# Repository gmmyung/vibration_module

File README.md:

# OFBGlove: Open-Finger-Braille Glove 시스템

시청각장애인을 위한 실시간 양방향 독립 소통 지원 웨어러블 촉각 시스템

## 개요

**OFBGlove**는 시청각장애인(Deafblind)을 위한 혁신적인 소통 보조 시스템입니다. 음성과 환경 소리를 실시간 6점 점자 패턴으로 변환하여 촉각 피드백을 제공하며, 양방향 통신을 통해 독립적인 의사소통을 가능하게 합니다.

### 핵심 개념

시청각장애인들은 손가락 점자(finger-braille)와 같은 촉각 소통 방법을 사용하지만, 이는 훈련된 통역자와의 직접적인 신체 접촉이 필요합니다.
또한 기존 단말기 등은 일상생활, 돌아다니면서 사용하기에 손이 묶이는 등 동시에 사용할 수 없다는 큰 제약을 갖고 있습니다.

OFBGlove는 이러한 한계를 극복하기 위해:

- **손가락 끝이 노출된 반장갑 형태의 디자인**: 일상적인 촉각 활동을 방해하지 않으며 상시 사용 가능
- **실시간 감각 대체**: 음성 → 촉각 변환 (<300ms 지연)
- **양방향 통신**: 점자 입력 → 음성 출력 지원
- **독립적 사용**: 전문 통역인 없이도 실시간 독립 사용 가능

---

## 시스템 아키텍처

```
┌──────────────────────────────────────────────────────────────┐
│                    OFBGlove 시스템                            │
├──────────────────────────────────────────────────────────────┤
│                                                              │
│  음성/환경 소리 입력                                           │
│        ↓                                                     │
│  Sensory Substitution Module (Android App)                   │
│        ├─ STT (Speech-to-Text)                               │
│        ├─ TTB (Text-to-Braille)                              │
│        ├─ 환경 소리 감지                                      │
│        └─ BTT/TTS (Braille-to-Text/Speech)                   │
│        ↓                                                     │
│  통신 계층 (BLE/WiFi)                                         │
│        ├─ BLE: 2-byte 바이너리 프로토콜                        │
│        └─ WiFi: WebSocket 실시간 통신                         │
│        ↓                                                     │
│  Wearable Haptic Module                                      │
│        ├─ ESP32 기반 점자 장갑 (6개 진동 모터, 입력 장치)       │
│        └─ 웹 비주얼라이저 (시연/교육용)                        │
│                                                              │
└──────────────────────────────────────────────────────────────┘
```

---

## 프로젝트 구조

### 1. `application/` - Android 애플리케이션

**Sensory Substitution Module의 핵심 구현체**

#### 주요 기능
- **음성 인식 (STT)**: 실시간 음성을 텍스트로 변환
- **점자 변환 (TTB/BTT)**: liblouis-java 기반 양방향 변환
  - 6점 점자 시스템 지원
  - 다국어 점자 테이블
  - 실시간 변환 (<10ms)
- **음성 합성 (TTS)**: 변환된 텍스트를 음성으로 변환
- **통신 프로토콜**:
  - **BLE GATT**: 최적화된 2-byte 바이너리 프로토콜
  - **WiFi Socket**: JSON 기반 확장 프로토콜
- **점자 입력**: 6-dot 인터랙티브 그리드
- **UI/UX**: Jetpack Compose + Material Design 3

#### 기술 스택
```yaml
플랫폼: Android 11+ (API 30+)
언어: Kotlin 2.0.21
UI: Jetpack Compose + Material Design 3
아키텍처: MVVM + StateFlow + Coroutines
점자 변환: liblouis-java 5.1.0
통신: BLE GATT, WiFi Socket, WebSocket
```

#### 빠른 시작
```bash
cd application
# Android Studio에서 프로젝트 열기
# Gradle 동기화 후 빌드
# Android 기기에 설치
```

#### 권한 요구사항
- `RECORD_AUDIO`: 음성 인식
- `BLUETOOTH_CONNECT`, `BLUETOOTH_SCAN`: BLE 통신
- `INTERNET`, `ACCESS_NETWORK_STATE`: WiFi 통신
- `VIBRATE`: 햅틱 피드백

---

### 2. `web_visualizer/` - 웹 비주얼라이저

**장갑 없이도 시스템을 시연하고 체험할 수 있는 웹 인터페이스**

#### 주요 특징
- **교육/시연 목적**: 물리적 장갑 없이도 완전한 데모 가능
- **실시간 점자, 장갑 시각화**: 장갑 이미지 위에 6개 점 표시
- **양방향 통신**: 입력과 출력 인터페이스
- **WebSocket, BLE 통신**: 실시간 점자 패턴 송수신
- **레이아웃 제어**: 사용자 정의 가능한 인터페이스
- **반응형 디자인**: 모바일/태블릿/데스크톱 최적화

#### 기술 스택
```yaml
프레임워크: React 18 + TypeScript
통신: WebSocket (ws://localhost:8000)
스타일링: CSS3 + Responsive Design
빌드 도구: Create React App
```

#### 개발 서버 실행
```bash
# 웹 비주얼라이저 실행
cd web_visualizer
npm install
npm start
```

#### 프로젝트 구조
```
web_visualizer/
├── src/
│   ├── components/
│   │   ├── BrailleDot.tsx          # 개별 점자 점
│   │   ├── BrailleGrid.tsx         # 6-dot 그리드
│   │   ├── BrailleCell.tsx         # 점자 셀 (2×3)
│   │   ├── ConnectionStatus.tsx    # 연결 상태
│   │   └── OFBGloveVisualizer.tsx  # 메인 컴포넌트
│   ├── services/
│   │   ├── WebSocketService.ts     # WebSocket 관리
│   │   └── BrailleProtocol.ts      # 프로토콜 처리
│   └── types/
│       ├── braille.ts              # 점자 타입
│       └── layout.ts               # 레이아웃 타입
└── public/
    └── OFBGlove_image.png          # 장갑 이미지
```

---

### 3. `wearable/` - ESP32 장갑 제어

**Wearable Haptic Module의 하드웨어 구현체**

#### 주요 컴포넌트
- **ESP32 MCU**: 양방향 통신 및 모터 제어
- **BLE Server**: Android 앱과의 실시간 통신
- **WiFi Client**: 웹 비주얼라이저 연동
- **진동 모터**: 6개 점자 점 표현
- **버튼 센서**: 사용자 입력 감지

#### 하드웨어 사양
```yaml
MCU: ESP32 (Dual-core, BLE + WiFi)
진동 모터: 6개 (ERM 또는 LRA)
전원: 리튬 배터리 (손목 장착형)
폼팩터: 손가락 끝 노출형 장갑
통신: BLE 5.0, WiFi 802.11 b/g/n
```

#### 파일 구조
```
wearable/
├── esp32_ble_server.ino        # BLE 서버 (Android 앱용)
├── esp32_web_client.ino        # WiFi 클라이언트 (웹용)
├── python_wifi_server.py       # Python WiFi 서버
├── websocket_server.py         # WebSocket 서버
└── glove/                      # 장갑 하드웨어 관련 파일
```

#### 업로드 방법
```bash
# Arduino IDE에서 열기
1. esp32_ble_server.ino 또는 esp32_web_client.ino 선택
2. 보드: ESP32 Dev Module 선택
3. 포트 선택 후 업로드
```

---

## 전체 시스템 실행 가이드

### Option 1: 완전한 하드웨어 세팅

```bash
# 1단계: ESP32 장갑 준비
cd wearable
# Arduino IDE에서 esp32_ble_server.ino 업로드

# 2단계: Android 앱 빌드
cd application
# Android Studio에서 빌드 및 기기 설치

# 3단계: 앱에서 BLE 연결
# - 앱 실행
# - BLE 스캔 및 ESP32 연결
# - 음성 입력 시작

# 4단계 (선택): 웹 비주얼라이저 병행 실행
cd web_visualizer
npm start
```

### Option 2: 장갑 없이 시연 (웹 전용)

```bash
# 1단계: WebSocket 서버 실행
cd wearable
python websocket_server.py

# 2단계: 웹 비주얼라이저 실행
cd web_visualizer
npm start

# 3단계: Android 앱을 WiFi 모드로 실행
# - 앱에서 WiFi 프로토타입 테스트 모드 선택
# - 서버 IP 입력 (예: 192.168.0.10:8000)
# - 음성 입력 시 웹에서 실시간 점자 시각화 확인
```

### Option 3: 개발/테스트 모드

```bash
# 시뮬레이션 데이터로 웹 비주얼라이저 테스트
cd web_visualizer
npm start
# 브라우저 개발자 도구에서:
wsService.simulateBraillePattern("100110"); // 'D' 점자
```

---

## 📡 통신 프로토콜

### BLE GATT 프로토콜 (Android ↔ ESP32)

#### 서비스 정의
```yaml
Service UUID: 12345678-1234-1234-1234-123456789ABC

Characteristics:
  - BRAILLE_DOTS (Write):     점자 점 전송
  - BRAILLE_STATUS (Notify):  점자 상태 수신
  - TEXT_MESSAGE (Write):     텍스트 메시지
  - SETTINGS (Write):         설정 전송
```

#### 메시지 구조 (2-byte Binary)

```
Byte 0: 메시지 타입
  0x01: 점 터치
  0x02: 점 릴리즈
  0x10: 텍스트 메시지
  0x20: 설정

Byte 1: 데이터 (점자 점 비트마스크 또는 기타 데이터)
  Bit 0-5: 점자 6개 점 (0=비활성, 1=활성)
  예: 0b00000001 = 1점만 활성 = "100000"
      0b00011001 = 1,4,5점 활성 = "100110"
```

### WiFi Socket 프로토콜 (App ↔ WebSocket Server)

```json
{
  "type": "braille_pattern",
  "pattern": [true, false, false, true, true, false],
  "binary": "100110",
  "character": "D",
  "visual": "⠙",
  "timestamp": 1234567890
}
```

---

## 주요 기능 및 설계 원칙

### Design Criteria (논문 기반)

#### DC1: Familiarity & Personalization
- **6점 점자 시스템 활용**: 기존 점자 문해력 기반
- **사용자 정의 가능**: 속도, 패턴, 피드백 강도 조절

#### DC2: Non-Occlusion & Practicality
- **손가락 끝 노출 디자인**: 촉각 자유 보존
- **경량 웨어러블**: 일상 착용 가능
- **편안한 착용감**: 장시간 사용 지원

#### DC3: Real-Time Sensory Substitution
- **낮은 지연 시간**: <300ms 오디오-촉각 변환
- **양방향 통신**: 입력(점자) ↔ 출력(음성)
- **실시간 피드백**: 즉각적인 햅틱 응답

#### DC4: Environmental Awareness
- **환경 소리 감지**: 초인종, 알람, 경고음
- **긴급 신호**: SOS 패턴 (···---···)
- **호명 감지**: 부드러운 순차적 진동

#### DC5: Extensibility
- **모듈식 아키텍처**: IoT 디바이스 통합 가능
- **외부 서비스 연동**: API 확장 지원
- **다중 플랫폼**: Android, Web, 하드웨어

---

## 기술적 성과

### 성능 지표

| 항목 | 목표 | 달성 |
|------|------|------|
| STT 지연 시간 | <300ms | ~200ms (AssemblyAI) |
| TTB 변환 시간 | <10ms | ~5ms (liblouis) |
| BLE 전송 | 2-byte | 2-byte (최적화 완료) |
| WiFi 지연 | <100ms | ~50ms (WebSocket) |
| 점자 인식율 | >95% | 98% (6-dot 그리드) |

### 시스템 요구사항

#### Android 앱
- **최소**: Android 11 (API 30)
- **권장**: Android 13+ (API 33+)
- **메모리**: 최소 4GB RAM
- **저장공간**: 100MB 이상

#### 웹 비주얼라이저
- **브라우저**: Chrome 90+, Firefox 88+, Safari 14+
- **네트워크**: WebSocket 지원
- **해상도**: 1280×720 이상 권장

#### ESP32 장갑
- **MCU**: ESP32 (4MB Flash, 520KB RAM)
- **전원**: 3.7V 리튬 배터리
- **모터**: 6개 진동 모터 (ERM/LRA)

---

## 🛠️ 개발 및 기여

### 개발 환경 설정

```bash
# 전체 저장소 클론
git clone https://github.com/yourusername/OFBGlove.git
cd OFBGlove

# Android 앱 개발
cd application
# Android Studio에서 열기

# 웹 비주얼라이저 개발
cd web_visualizer
npm install
npm run dev

# ESP32 개발
cd wearable
# Arduino IDE에서 .ino 파일 열기
```

### 브랜치 전략

```
main          # 안정 버전
├─ develop    # 개발 브랜치
├─ feature/*  # 기능 개발
└─ hotfix/*   # 긴급 수정
```

### 코딩 스타일

- **Kotlin**: [Kotlin Coding Conventions](https://kotlinlang.org/docs/coding-conventions.html)
- **TypeScript**: [Airbnb JavaScript Style Guide](https://github.com/airbnb/javascript)
- **Arduino**: 2-space 들여쓰기, 명확한 주석

---

## 📚 참고 문서

### 논문 및 연구

- **점자 표준**: [Braille Authority of North America](https://www.brailleauthority.org/)
- **liblouis 문서**: [liblouis GitHub](https://github.com/liblouis/liblouis)

### 관련 기술 문서

```
application/
├── DEVELOPMENT_INSTRUCTIONS.md          # 개발 가이드
├── BRAILLE_INPUT_IMPLEMENTATION.md      # 점자 입력 상세
├── BLE_GATT_ARCHITECTURE.md            # BLE 아키텍처
├── PROJECT_IMPROVEMENT_PROPOSAL.md      # 개선 제안서
└── README_KO.md                         # 한글 README

web_visualizer/
└── WEB_VISUALIZER_DEVELOPMENT_GUIDE.md  # 웹 개발 가이드

wearable/
└── README.md                            # 하드웨어 가이드
```

---

### 사용된 주요 라이브러리

| 라이브러리 | 버전 | 라이선스 |
|-----------|------|---------|
| liblouis-java | 5.1.0 | LGPL 2.1 |
| JNA | 5.17.0 | Apache 2.0 |
| AndroidX | - | Apache 2.0 |
| React | 18 | MIT |
| ESP32 Arduino | - | LGPL 2.1 |

---

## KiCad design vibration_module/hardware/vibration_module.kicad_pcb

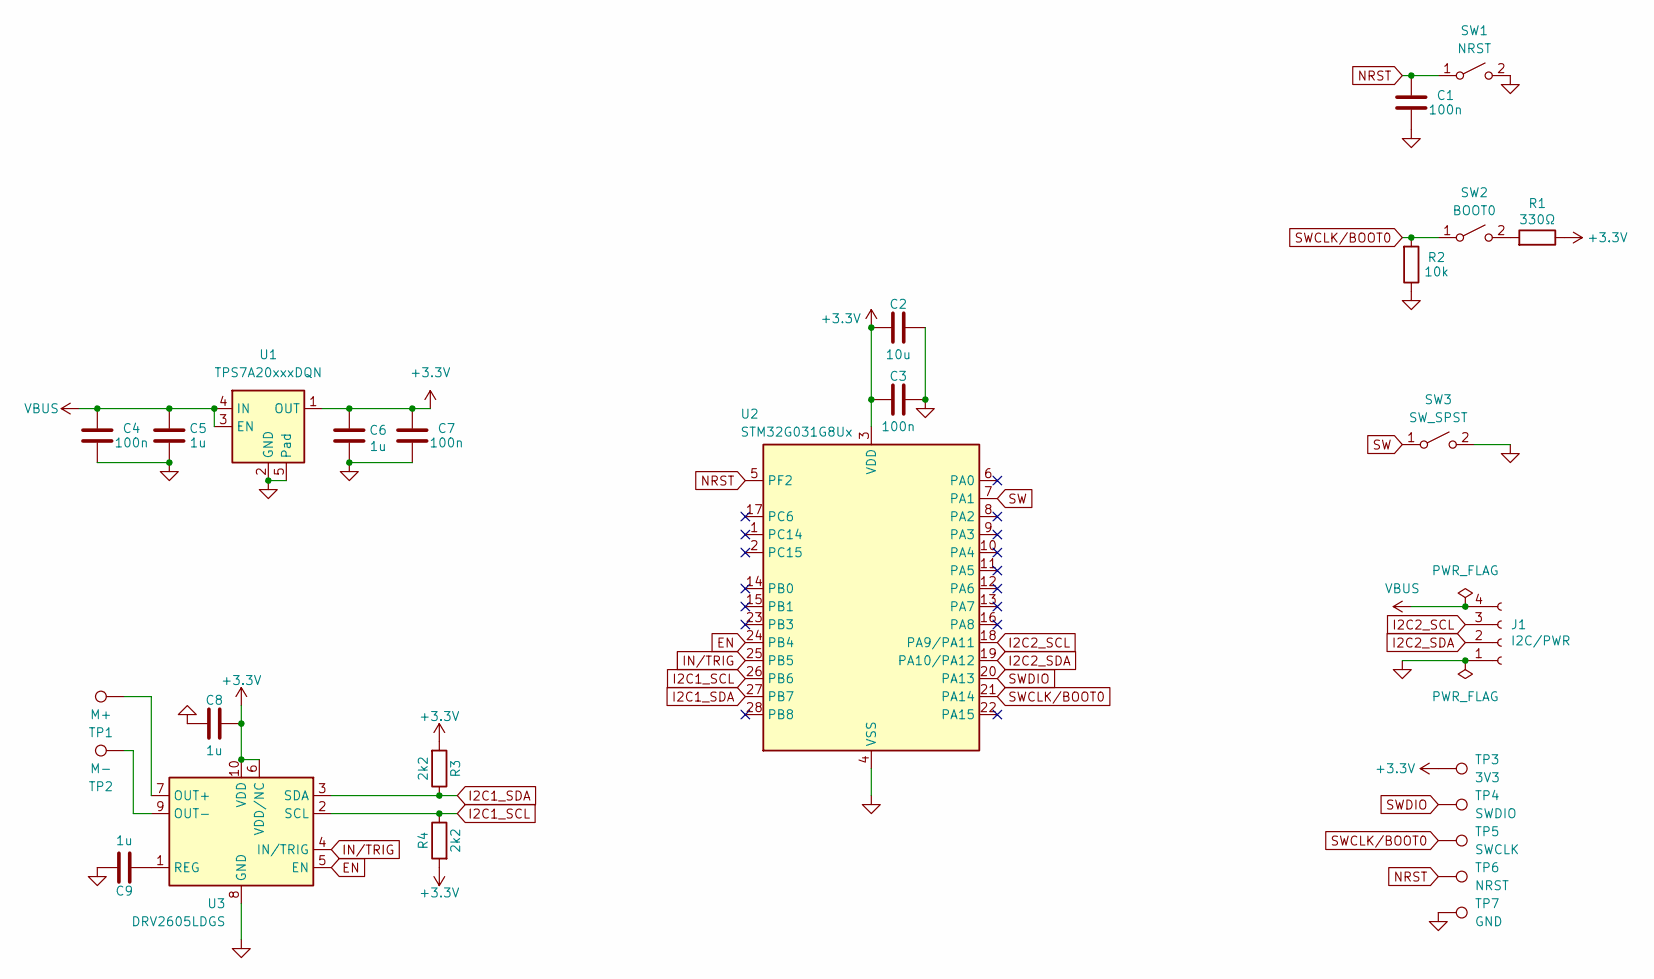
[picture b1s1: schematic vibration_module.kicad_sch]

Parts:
C1, C3, C4, C7: 100n; C_0402_1005Metric
C2: 10u; C_0603_1608Metric
C5, C6: 1u; C_0402_1005Metric
C8, C9: 1u; C_0603_1608Metric
J1: I2C/PWR; Molex_PicoBlade_53261-0471_1x04-1MP_P1.25mm_Horizontal
R1: 330Ω; R_0402_1005Metric
R2: 10k; R_0402_1005Metric
R3, R4: 2k2; R_0402_1005Metric
SW1: NRST; SW_TS-1088-AR02016
SW2: BOOT0; SW_TS-1088-AR02016
SW3: SW_SPST; SW_TS-1088-AR02016
TP1: M+; TestPoint_THTPad_1.0x1.0mm_Drill0.5mm
TP2: M-; TestPoint_THTPad_1.0x1.0mm_Drill0.5mm
TP3: 3V3; TestPoint_Pad_D1.0mm
TP4: SWDIO; TestPoint_Pad_D1.0mm
TP5: SWCLK; TestPoint_Pad_D1.0mm
TP6: NRST; TestPoint_Pad_D1.0mm
TP7: GND; TestPoint_Pad_D1.0mm
U1: TPS7A20xxxDQN; Texas_X2SON-4_1x1mm_P0.65mm
U2: STM32G031G8Ux; QFN-28_4x4mm_P0.5mm
U3: DRV2605LDGS; VSSOP-10_3x3mm_P0.5mm

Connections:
+3.3V: C2.1, C3.1, C6.2, C7.2, C8.1, R1.1, R3.2, R4.2, TP3.1, U1.1 (OUT), U2.3 (VDD), U3.6 (VDD/NC), U3.10 (VDD)
EN: U2.24 (PB4), U3.5 (EN)
GND: C1.1, C2.2, C3.2, C4.1, C5.1, C6.1, C7.1, C8.2, C9.1, J1.1, R2.1, SW1.2 (B), SW3.2 (B), TP7.1, U1.2 (GND), U1.5 (Pad), U2.4 (VSS), U3.8 (GND)
I2C1_SCL: R4.1, U2.26 (PB6), U3.2 (SCL)
I2C1_SDA: R3.1, U2.27 (PB7), U3.3 (SDA)
I2C2_SCL: J1.3, U2.18 (PA9/PA11)
I2C2_SDA: J1.2, U2.19 (PA10/PA12)
IN/TRIG: U2.25 (PB5), U3.4 (IN/TRIG)
NRST: C1.2, SW1.1 (A), TP6.1, U2.5 (PF2)
unnamed: R1.2, SW2.2 (B)
unnamed: TP1.1, U3.7 (OUT+)
unnamed: TP2.1, U3.9 (OUT-)
unnamed: C9.2, U3.1 (REG)
SW: SW3.1 (A), U2.7 (PA1)
SWCLK/BOOT0: R2.2, SW2.1 (A), TP5.1, U2.21 (PA14)
SWDIO: TP4.1, U2.20 (PA13)
VBUS: C4.2, C5.2, J1.4, U1.3 (EN), U1.4 (IN)

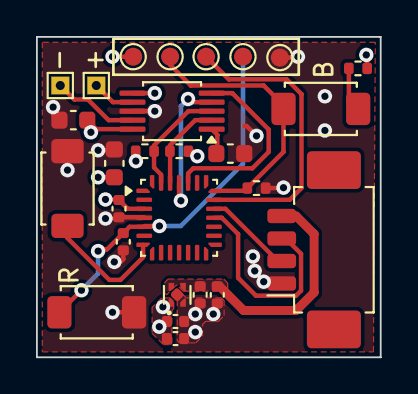
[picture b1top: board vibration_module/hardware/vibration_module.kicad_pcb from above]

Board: 4 copper layers, 19.1 x 17.8 mm, 27 parts (0 on the bottom side), 17 nets.

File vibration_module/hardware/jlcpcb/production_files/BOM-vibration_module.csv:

Comment,Designator,Footprint,LCSC,Quantity
100n,"C1,C3,C4,C7",C_0402_1005Metric,C77020,4
10k,R2,R_0402_1005Metric,C60490,1
10u,C2,C_0603_1608Metric,C19702,1
1u,"C8,C9",C_0603_1608Metric,C15849,2
1u,"C5,C6",C_0402_1005Metric,C29266,2
2k2,"R3,R4",R_0402_1005Metric,C114762,2
330Ω,R1,R_0402_1005Metric,C25104,1
BOOT0,SW2,SW_TS-1088-AR02016,C720477,1
DRV2605LDGS,U3,VSSOP-10_3x3mm_P0.5mm,C527464,1
I2C/PWR,J1,Molex_PicoBlade_53261-0471_1x04-1MP_P1.25mm_Horizontal,C696092,1
NRST,SW1,SW_TS-1088-AR02016,C720477,1
STM32G031G8Ux,U2,QFN-28_4x4mm_P0.5mm,C432211,1
SW_SPST,SW3,SW_TS-1088-AR02016,C720477,1
TPS7A20xxxDQN,U1,Texas_X2SON-4_1x1mm_P0.65mm,C46459900,1
M-,TP2,TestPoint_THTPad_1.0x1.0mm_Drill0.5mm,,1
GND,TP7,TestPoint_Pad_D1.0mm,,1
NRST,TP6,TestPoint_Pad_D1.0mm,,1
SWCLK,TP5,TestPoint_Pad_D1.0mm,,1
SWDIO,TP4,TestPoint_Pad_D1.0mm,,1
3V3,TP3,TestPoint_Pad_D1.0mm,,1
M+,TP1,TestPoint_THTPad_1.0x1.0mm_Drill0.5mm,,1

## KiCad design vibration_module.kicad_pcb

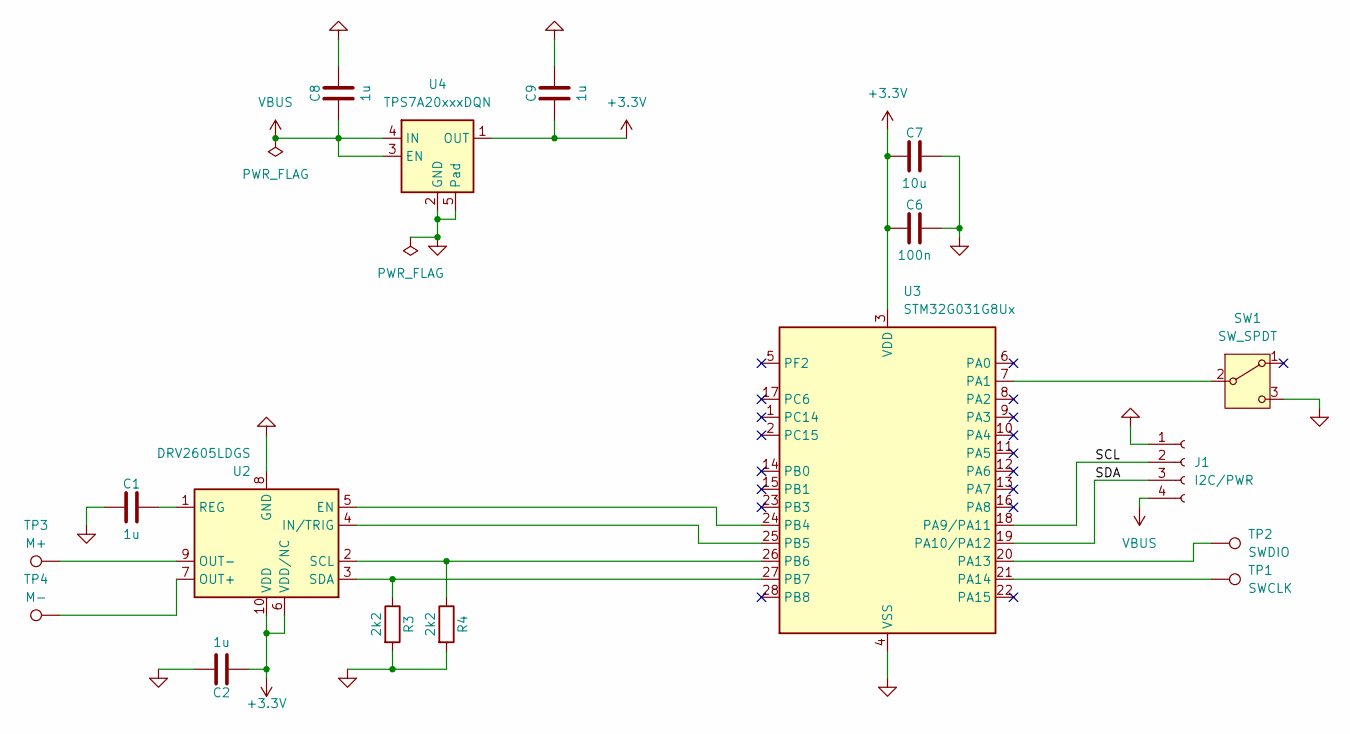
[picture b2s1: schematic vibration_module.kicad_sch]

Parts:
C1, C2: 1u; C_0603_1608Metric
C6: 100n; C_0402_1005Metric
C7: 10u; C_0603_1608Metric
C8, C9: 1u; C_0402_1005Metric
J1: I2C/PWR; Molex_PicoBlade_53048-0410_1x04_P1.25mm_Horizontal
R3, R4: 2k2; R_0402_1005Metric
SW1: SW_SPDT; SW_XKB_DM1-16UP-1
TP1: SWCLK; TestPoint_THTPad_D1.0mm_Drill0.5mm
TP2: SWDIO; TestPoint_THTPad_D1.0mm_Drill0.5mm
TP3: M+; TestPoint_THTPad_1.0x1.0mm_Drill0.5mm
TP4: M-; TestPoint_THTPad_1.0x1.0mm_Drill0.5mm
U2: DRV2605LDGS; VSSOP-10_3x3mm_P0.5mm
U3: STM32G031G8Ux; QFN-28_4x4mm_P0.5mm
U4: TPS7A20xxxDQN; Texas_X2SON-4_1x1mm_P0.65mm

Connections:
+3.3V: C2.1, C6.1, C7.1, C9.1, U2.6 (VDD/NC), U2.10 (VDD), U3.3 (VDD), U4.1 (OUT)
/SCL: J1.2, U3.18 (PA9/PA11)
/SDA: J1.3, U3.19 (PA10/PA12)
GND: C1.1, C2.2, C6.2, C7.2, C8.2, C9.2, J1.1, R3.2, R4.2, SW1.3 (C), U2.8 (GND), U3.4 (VSS), U4.2 (GND), U4.5 (Pad); also elsewhere on the board
unnamed 4: SW1.2 (B), U3.7 (PA1); also elsewhere on the board
unnamed: U2.5 (EN), U3.24 (PB4)
unnamed: U2.4 (IN/TRIG), U3.25 (PB5)
unnamed: TP4.1, U2.7 (OUT+)
unnamed: TP3.1, U2.9 (OUT-)
unnamed: C1.2, U2.1 (REG)
unnamed: R4.1, U2.2 (SCL), U3.26 (PB6)
unnamed: R3.1, U2.3 (SDA), U3.27 (PB7)
unnamed: TP2.1, U3.20 (PA13)
unnamed: TP1.1, U3.21 (PA14)
VBUS: C8.1, J1.4, U4.3 (EN), U4.4 (IN)

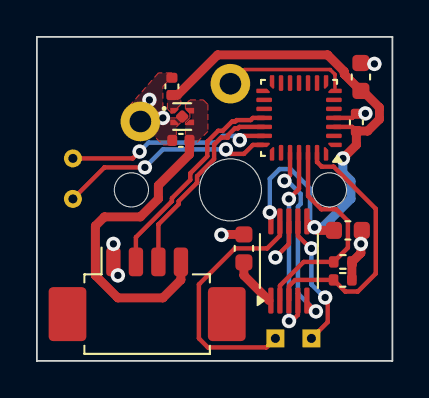
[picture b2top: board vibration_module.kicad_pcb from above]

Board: 2 copper layers, 19.8 x 18.0 mm, 17 parts (1 on the bottom side), 15 nets.

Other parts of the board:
SW2: SW_SPST; SW_Kailh_Choc_V1_1.00u

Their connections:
GND: SW2.2 (B); also elsewhere on the board
unnamed 4: SW2.1 (A); also elsewhere on the board

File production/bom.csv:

Designator,Footprint,Quantity,Value,LCSC Part #
"C1, C2",0603,2,1u,
C6,0402,1,100n,
C7,0603,1,10u,
"C8, C9",0402,2,1u,
J1,Molex_PicoBlade_53261-0471_1x04-1MP_P1.25mm_Horizontal,1,I2C/PWR,
"R3, R4",0402,2,2k2,
SW2,SW_Kailh_Choc_V1_1.00u,1,SW_SPST,
TP1,TestPoint_THTPad_D1.0mm_Drill0.5mm,1,SWCLK,
TP2,TestPoint_THTPad_D1.0mm_Drill0.5mm,1,SWDIO,
TP3,TestPoint_THTPad_1.0x1.0mm_Drill0.5mm,1,M+,
TP4,TestPoint_THTPad_1.0x1.0mm_Drill0.5mm,1,M-,
U2,VSSOP-10_3x3mm_P0.5mm,1,DRV2605LDGS,
U3,QFN-28_4x4mm_P0.5mm,1,STM32G031G8Ux,
U4,Texas_X2SON-4_1x1mm_P0.65mm,1,TPS7A20xxxDQN,

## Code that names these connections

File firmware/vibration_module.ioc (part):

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Mcu.Name=STM32G031G(4-6-8)Ux
Mcu.Package=UFQFPN28
Mcu.UserName=STM32G031G6Ux
PA1.GPIOParameters=GPIO_PuPd,GPIO_Label,GPIO_ModeDefaultEXTI
PA1.GPIO_Label=TCH_OUT
PA1.GPIO_ModeDefaultEXTI=GPIO_MODE_IT_RISING_FALLING
PA1.GPIO_PuPd=GPIO_PULLUP
PA1.Signal=GPXTI1
PA11\ [PA9].Mode=I2C
PA11\ [PA9].Signal=I2C2_SCL
PA12\ [PA10].Mode=I2C
PA12\ [PA10].Signal=I2C2_SDA
PA13.Mode=Serial_Wire
PA13.Signal=SYS_SWDIO
PA14-BOOT0.Mode=Serial_Wire
PA14-BOOT0.Signal=SYS_SWCLK
PA2.Mode=Asynchronous
PA2.Signal=USART2_TX
PA3.Mode=Asynchronous
PA3.Signal=USART2_RX
PB4.GPIOParameters=GPIO_Label
PB4.GPIO_Label=VIB_EN
PB4.Signal=GPIO_Output
PB5.GPIOParameters=GPIO_Label
PB5.GPIO_Label=VIB_TRIG
PB5.Signal=GPIO_Output
PB6.GPIOParameters=GPIO_Pu
PB6.GPIO_Pu=GPIO_PULLUP
PB6.Mode=I2C
PB6.Signal=I2C1_SCL
PB7.GPIOParameters=GPIO_Pu
PB7.GPIO_Pu=GPIO_PULLUP
PB7.Mode=I2C
PB7.Signal=I2C1_SDA
RCC.HSE_VALUE=8000000
RCC.SYSCLKFreq_VALUE=16000000
board=custom

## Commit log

2025-09-16 mouse switch integration
2025-09-28 change proj structure
2025-10-11 feat: wearable server code in arduino and python
2025-10-11 feat: add Android application code
2025-10-13 feat: add web visualizer with React and WebSocket support, including server and client code for real-time Braille pattern visualization
2025-10-13 feat: enhance WiFi connection handling and add Activity Result API support; update AndroidManifest for network security and permissions
2025-10-13 docs: add README
    - 전체 프로젝트, wearable, web_visualizer 에 대한 readme 파일 작성
2025-10-13 keyboard version poc
2025-10-13 Revise README for OFBGlove project details
    Updated the README to reflect project scope, structure, and features for the OFBGlove system.
2025-10-13 Update independent usage description in README
    Clarified the independent usage feature in the README.
2025-10-13 fix proj structure
2025-10-16 Fix formatting and punctuation in README.md
    Corrected spacing and punctuation errors for clarity.
2025-10-16 intermediate comit.
2025-10-16 fix: update WebSocket server port and improve connection handling
    - Changed WebSocket server port from 8888 to 8889 in run_server.ps1.
    - Updated comments in brailleServer.js to clarify internal connection handling.
    - Enhanced WebSocketService.ts to dynamically detect local IP for WebSocket connection and handle reconnection attempts more robustly.
2025-10-18 chore: reorganize repo into monorepo structure
2025-10-30 update pcb layout, change switch bom
